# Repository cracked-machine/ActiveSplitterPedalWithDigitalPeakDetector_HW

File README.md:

## Active 4-way splitter pedal with digital peak detector

- Analog 1->4 splitter circuit with buffered input and output gain controls.
- Digital LED peak detector per output channel.
- Fits in a Hammond 1590BB enclosure (120mm x 95mm).

Required Kicad Hardware library: https://github.com/cracked-machine/KicadLibrary

Related SW project: https://github.com/cracked-machine/DigitalPeakDetector_SW

### System Overview

### Schematic

##### Top Level

##### Input Buffer and Gain Block

This uses a split supply op amp. The second stage is an inverting op amp configuration so that it can attenuate the input signal down to zero output.
Therefore the second op amp has very low input impedance and will cause "tone-suck" if used on its own. The solution is to add a preceding op amp stage in a non-inverting configuration that works as a high input impedance buffer.

##### Negative Rail Block

Each ``Input Buffer and Gain Block`` requires a split power supply. We use a charge pump to provide a negative voltage rail. The small SOT23-5 package provides ~10mA current, which is enough for a dual opamp in this design.

##### MCU Peak Detector block

This section replaces the classic analog peak detector circuit with a microcontroller. The input signal is captured by the 12bit ADC of the microcontroller. The average input value and the output threshold are determined by software. When the output threshold is reached, the microcontroller briefly toggles the LED. The on/off time duration of the LED is also determined in software.

##### MCU Input Buffer block

This serves several purposes.
1. It acts as a high impedance buffer and low pass filter for the ADC. This helps to provide a cleaner input signal for the ADC by removing high frequency noise.
2. The 3.3V *single* supply of the op amp removes any parts of the input signal that swing above 3.3v and below ground (the limits of the microcontroller). In the event that a line level input signal was plugged into the input, the op amp would be damaged before the microcontroller.

##### Power Supply block

This linear regulator drops the 9VDC input to 3.3VDC. The power requirements of the system components are very low (~65mA) so the expected dissipation is also low (0.37W). A copper pad on both sides of the PCB (with connected vias) is provided to reduce this dissipation.

## 3D Renderings

__PCB__

__Front Panel__

__Back Panel__

This is the same back panel used for
[ActiveMixerPedalWithDigitalPeakDetector_HW ](https://github.com/cracked-machine/ActiveMixerPedalWithDigitalPeakDetector_HW)

__PCB and panel profile__

## TODO

Some issues with the HW design:

- The PSU uses 3.3V for both MCU and Analog blocks. This is too low for the opamps in the analog blocks and does not allow enough headroom for the signal. This can result in clipping of the signal.

- The charge pumps used by the opamps in the analog blocks (used to create a negative voltage rail) need filtering. The negative voltage rail is noisy (observed on the scope) and a high pitched whine can be heard through the output when plugged into a large amplifier. A simple passive LPF would probably solve this. 

- The input is on the wrong side!

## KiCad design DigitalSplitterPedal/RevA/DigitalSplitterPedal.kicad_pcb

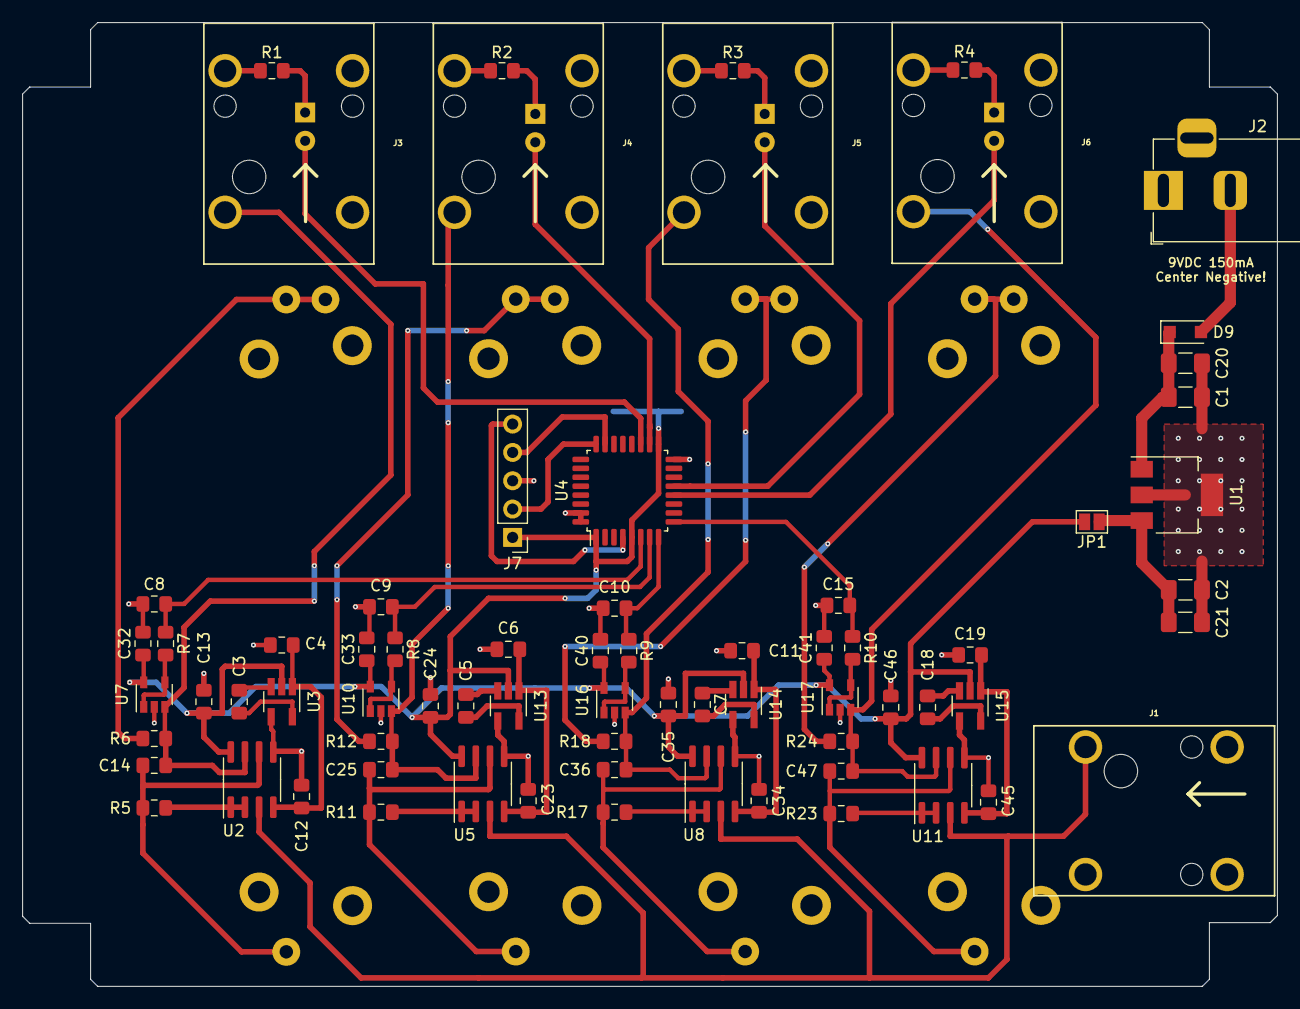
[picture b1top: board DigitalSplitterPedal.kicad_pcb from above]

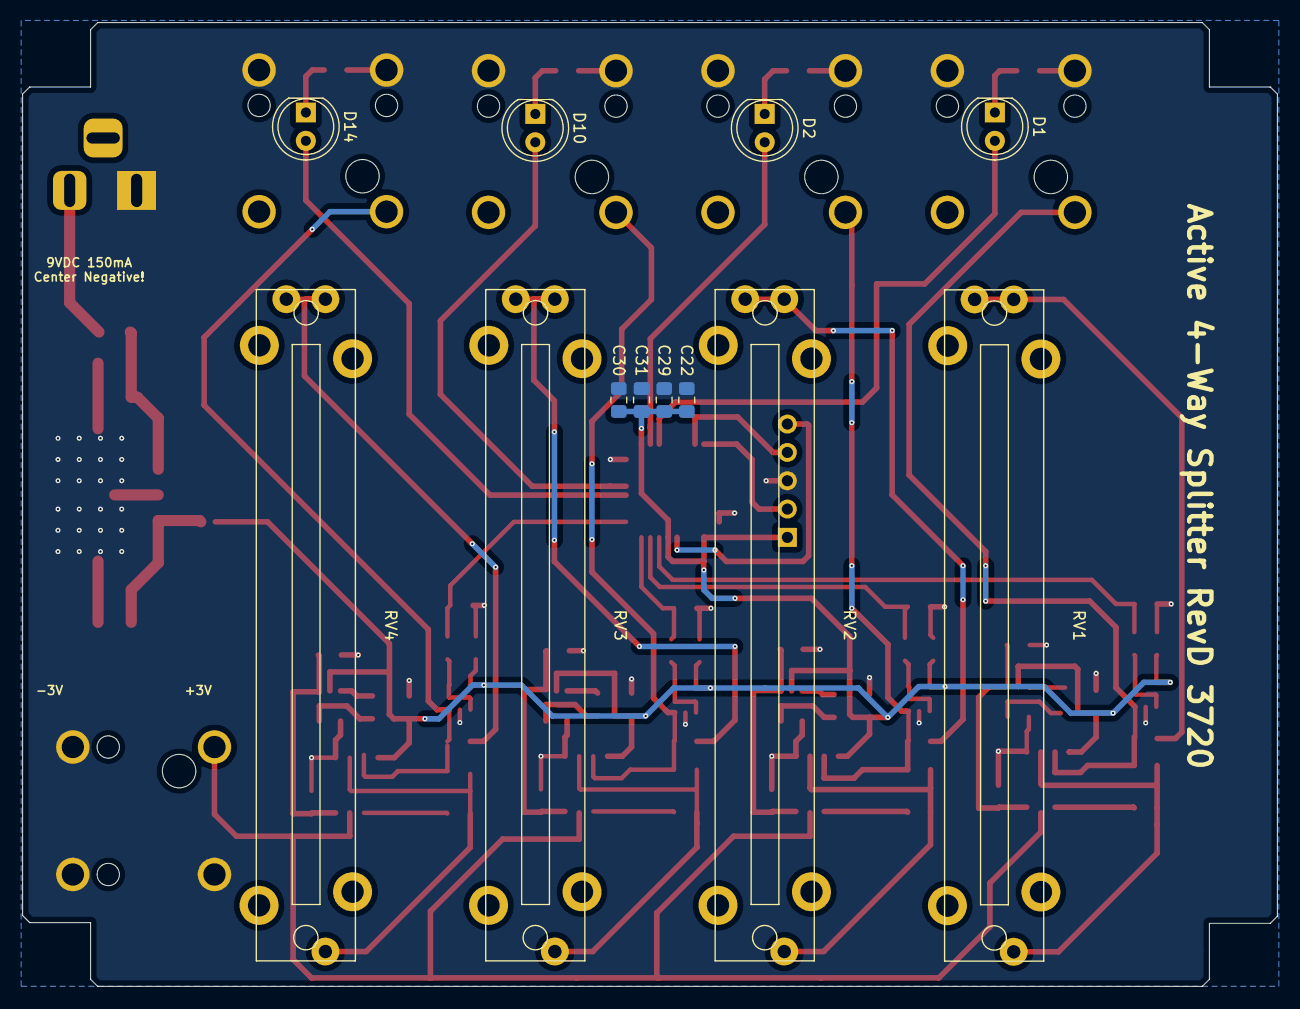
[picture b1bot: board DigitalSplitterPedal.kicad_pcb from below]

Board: 2 copper layers, 112.5 x 86.4 mm, 83 parts (12 on the bottom side), 53 nets.

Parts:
C1, C21: 100nF; C_1206_3216Metric_Pad1.42x1.75mm_HandSolder
C2, C20: 1uF; C_1206_3216Metric_Pad1.42x1.75mm_HandSolder
C3, C4, C5, C6, C7, C11, C18, C19, C22: 1uF; C_0805_2012Metric_Pad1.15x1.40mm_HandSolder
C8, C9, C10, C12, C13, C15, C23, C24, C29, C30, C31, C32, C33, C34, C35, C40, C41, C45, C46: 100nF; C_0805_2012Metric_Pad1.15x1.40mm_HandSolder
C14, C25, C36, C47: 1nF; C_0805_2012Metric_Pad1.15x1.40mm_HandSolder
D1, D2, D10, D14: LED; LED_D5.0mm
D9: B0520LW-RH; D_SOD-123F
J1, J3, J4, J5, J6: MonoJack2Switch; NRJxHx
J2: Barrel_Jack; BarrelJack_Horizontal
J7: Conn_01x05; PinHeader_1x05_P2.54mm_Vertical
JP1: Jumper_NO_Small; SolderJumper-2_P1.3mm_Open_Pad1.0x1.5mm
R1, R2, R3, R4: R; R_0805_2012Metric_Pad1.15x1.40mm_HandSolder
R5, R11, R17, R23: 560R; R_0805_2012Metric_Pad1.15x1.40mm_HandSolder
R6, R12, R18, R24: 100R; R_0805_2012Metric_Pad1.15x1.40mm_HandSolder
R7, R8, R9, R10: 50R; R_0805_2012Metric_Pad1.15x1.40mm_HandSolder
RV1, RV2, RV3, RV4: 1K; Slider_PTA4543_60MM
U1: MCP1703A-3302_SOT223; SOT-223-3_TabPin2
U2, U5, U8, U11: TL072; SOIC-8_3.9x4.9mm_P1.27mm
U3, U13, U14, U15: TPS60400; SOT-23-5_HandSoldering
U4: STM32F051K8Tx; LQFP-32_7x7mm_P0.8mm
U7, U10, U16, U17: MCP601-xOT; SOT-23-5

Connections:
+3V3: C13.1, C22.1, C24.1, C29.1, C30.1, C31.1, C32.1, C33.1, C35.1, C40.1, C41.1, C46.1, J7.1, JP1.2, U2.8, U3.2, U4.1, U4.5, U4.17, U5.8, U7.5, U8.8, U10.5, U11.8, U13.2, U14.2, U15.2, U16.5, U17.5
/InputBufferAndGain1/NEGVIN: C4.1, C12.1, U2.4, U3.1
/InputBufferAndGain1/SIGNAL_INPUT: J1.1, U2.3, U5.3, U8.3, U11.3
/InputBufferAndGain2/NEGVIN: C6.1, C23.1, U5.4, U13.1
/InputBufferAndGain3/NEGVIN: C11.1, C34.1, U8.4, U14.1
/InputBufferAndGain4/NEGVIN: C19.1, C45.1, U11.4, U15.1
/PEAK_IN_BUF1: C14.1, J3.1, R6.1, U2.7, U7.3
/PEAK_IN_BUF2: C25.1, J4.1, R12.1, U5.7, U10.3
/PEAK_IN_BUF3: C36.1, J5.1, R18.1, U8.7, U16.3
/PEAK_IN_BUF4: C47.1, J6.1, R24.1, U11.7, U17.3
/PeakDetectorMCU/NRST: J7.5, U4.4
/PeakDetectorMCU/PEAK_IN_ADC1: C8.1, R7.1, U4.6
/PeakDetectorMCU/PEAK_IN_ADC2: C9.1, R8.1, U4.7
/PeakDetectorMCU/PEAK_IN_ADC3: C10.1, R9.1, U4.8
/PeakDetectorMCU/PEAK_IN_ADC4: C15.1, R10.1, U4.9
/PeakDetectorMCU/PEAK_OUT_PWM1: D14.2, U4.12
/PeakDetectorMCU/PEAK_OUT_PWM2: D10.2, U4.13
/PeakDetectorMCU/PEAK_OUT_PWM3: D2.2, U4.18
/PeakDetectorMCU/PEAK_OUT_PWM4: D1.2, U4.19
/PeakDetectorMCU/SYS_SWCLK: J7.2, U4.24
/PeakDetectorMCU/SYS_SWDIO: J7.4, U4.23
/PowerSupply/+9V_IN: D9.2, J2.2
GNDS: C1.2, C2.2, C4.2, C6.2, C8.2, C9.2, C10.2, C11.2, C12.2, C13.2, C15.2, C19.2, C20.2, C21.2, C22.2, C23.2, C24.2, C29.2, C30.2, C31.2, C32.2, C33.2, C34.2, C35.2, C40.2, C41.2, C45.2, C46.2, J1.2, J1.3, J1.4, J2.1, J3.3, J3.4, J4.3, J4.4, J5.3, J5.4, J6.3, J6.4, J7.3, R1.1, R2.1, R3.1, R4.1, U1.2, U2.5, U3.4, U4.16, U4.31, U4.32, U5.5, U7.2, U8.5, U10.2, U11.5, U13.4, U14.4, U15.4, U16.2, U17.2
unnamed: C1.1, C20.1, D9.1, U1.1
unnamed: C2.1, C21.1, JP1.1, U1.3
unnamed: C3.1, U3.3
unnamed: C3.2, U3.5
unnamed: C5.1, U13.3
unnamed: C5.2, U13.5
unnamed: C7.1, U14.3
unnamed: C7.2, U14.5
unnamed: C14.2, R5.1, RV1.3, U2.6
unnamed: C18.1, U15.3
unnamed: C18.2, U15.5
unnamed: C25.2, R11.1, RV2.3, U5.6
unnamed: C36.2, R17.1, RV3.3, U8.6
unnamed: C47.2, R23.1, RV4.3, U11.6
unnamed: D1.1, R1.2
unnamed: D2.1, R2.2
unnamed: D10.1, R3.2
unnamed: D14.1, R4.2
unnamed: R5.2, U2.1, U2.2
unnamed: R6.2, RV1.1, RV1.2
unnamed: R7.2, U7.1, U7.4
unnamed: R8.2, U10.1, U10.4
unnamed: R9.2, U16.1, U16.4
unnamed: R10.2, U17.1, U17.4
unnamed: R11.2, U5.1, U5.2
unnamed: R12.2, RV2.1, RV2.2
unnamed: R17.2, U8.1, U8.2
unnamed: R18.2, RV3.1, RV3.2
unnamed: R23.2, U11.1, U11.2
unnamed: R24.2, RV4.1, RV4.2

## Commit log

2020-09-23 hw update
    RevA schematic complete,
    TODO: RevA layout
2020-09-24 HW update
    - Completed RevA layout (draft)
2020-09-25 updated hw
    - add testpoints
2020-09-25 updated readme
    add system overview block diagram
2020-09-25 updated readme
    - updated system overview diagram
2020-09-26 updated system overview diagram
2020-09-26 updated name, paths and readme
2020-09-26 updated readme
    added description
2020-09-26 updated readme
    added schema svg
2020-10-11 Added front/back panels, updated readme
2020-10-12 updated front/back panel layout and gerbers
    - Changed mount holes to non-via
    - Changed BCu plane to FCu plane (same side as FCu silkscreen)
2020-10-13 Added EnclosureInternalVerticalMeasurement.svg
2020-10-16 revised readme and added comments
2020-10-23 hw update
    moved led resistors to back copper layer
2020-10-23 schematic update
    updated resistor (Rin) to 1K/10K
2020-10-24 updated front panel layout
    moved silk screen
